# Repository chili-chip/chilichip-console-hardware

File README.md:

# chilichip console board

KiCad project for the all-in-one chilichip console PCB: the main board and all modules (RP2350, 2.0" screen, audio, radio, sensors, haptics, buttons) on one fully assembled board. 50 × 83.9 mm, 4 layers, fits the Slab casing.

**Status:** schematic, placement and routing done. 3 connections at the RP2350 still open (see docs, open points). Not built.

| Front | Back |
|---|---|
|  |  |

## Docs

The MkDocs site in `docs/` has the design, pin map, power tree, schematics, layout, parts list and open points. Run `pip install -r docs/requirements.txt && mkdocs serve`.

## Files

| Path | What it is |
|---|---|
| `chilichip-console.kicad_pro` and sheets | KiCad 10 project |
| `scripts/` | Generators: `design.py` holds every part and net |
| `reference/rp2350a-minimal/` | Raspberry Pi's RP2350A minimal design, unchanged |

## Credits

The RP2350A circuit comes from Raspberry Pi's **RP2350A minimal design** ([hardware design with RP2350](https://datasheets.raspberrypi.com/rp2350/hardware-design-with-rp2350.pdf)). Thanks to Raspberry Pi Ltd for publishing it. The GBA button footprints are from [Pigweed Kudzu](https://pigweed.googlesource.com/pigweed/kudzu/+/refs/heads/main/pcb/), CC BY 4.0.

## Licence

MIT, see [LICENSE.txt](LICENSE.txt). The copyright notice is Raspberry Pi Ltd's and stays in place; chilichip's changes are added next to it.

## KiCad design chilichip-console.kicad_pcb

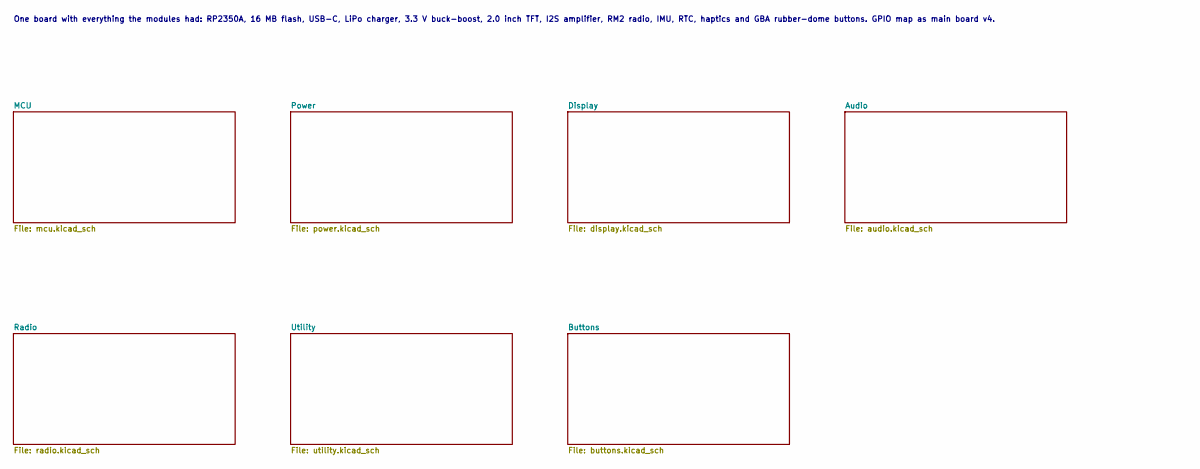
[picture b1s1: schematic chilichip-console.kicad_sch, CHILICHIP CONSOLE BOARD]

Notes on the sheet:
One board with everything the modules had: RP2350A, 16 MB flash, USB-C, LiPo charger, 3.3 V buck-boost, 2.0 inch TFT, I2S amplifier, RM2 radio, IMU, RTC, haptics and GBA rubber-dome buttons. GPIO map as main board v4.

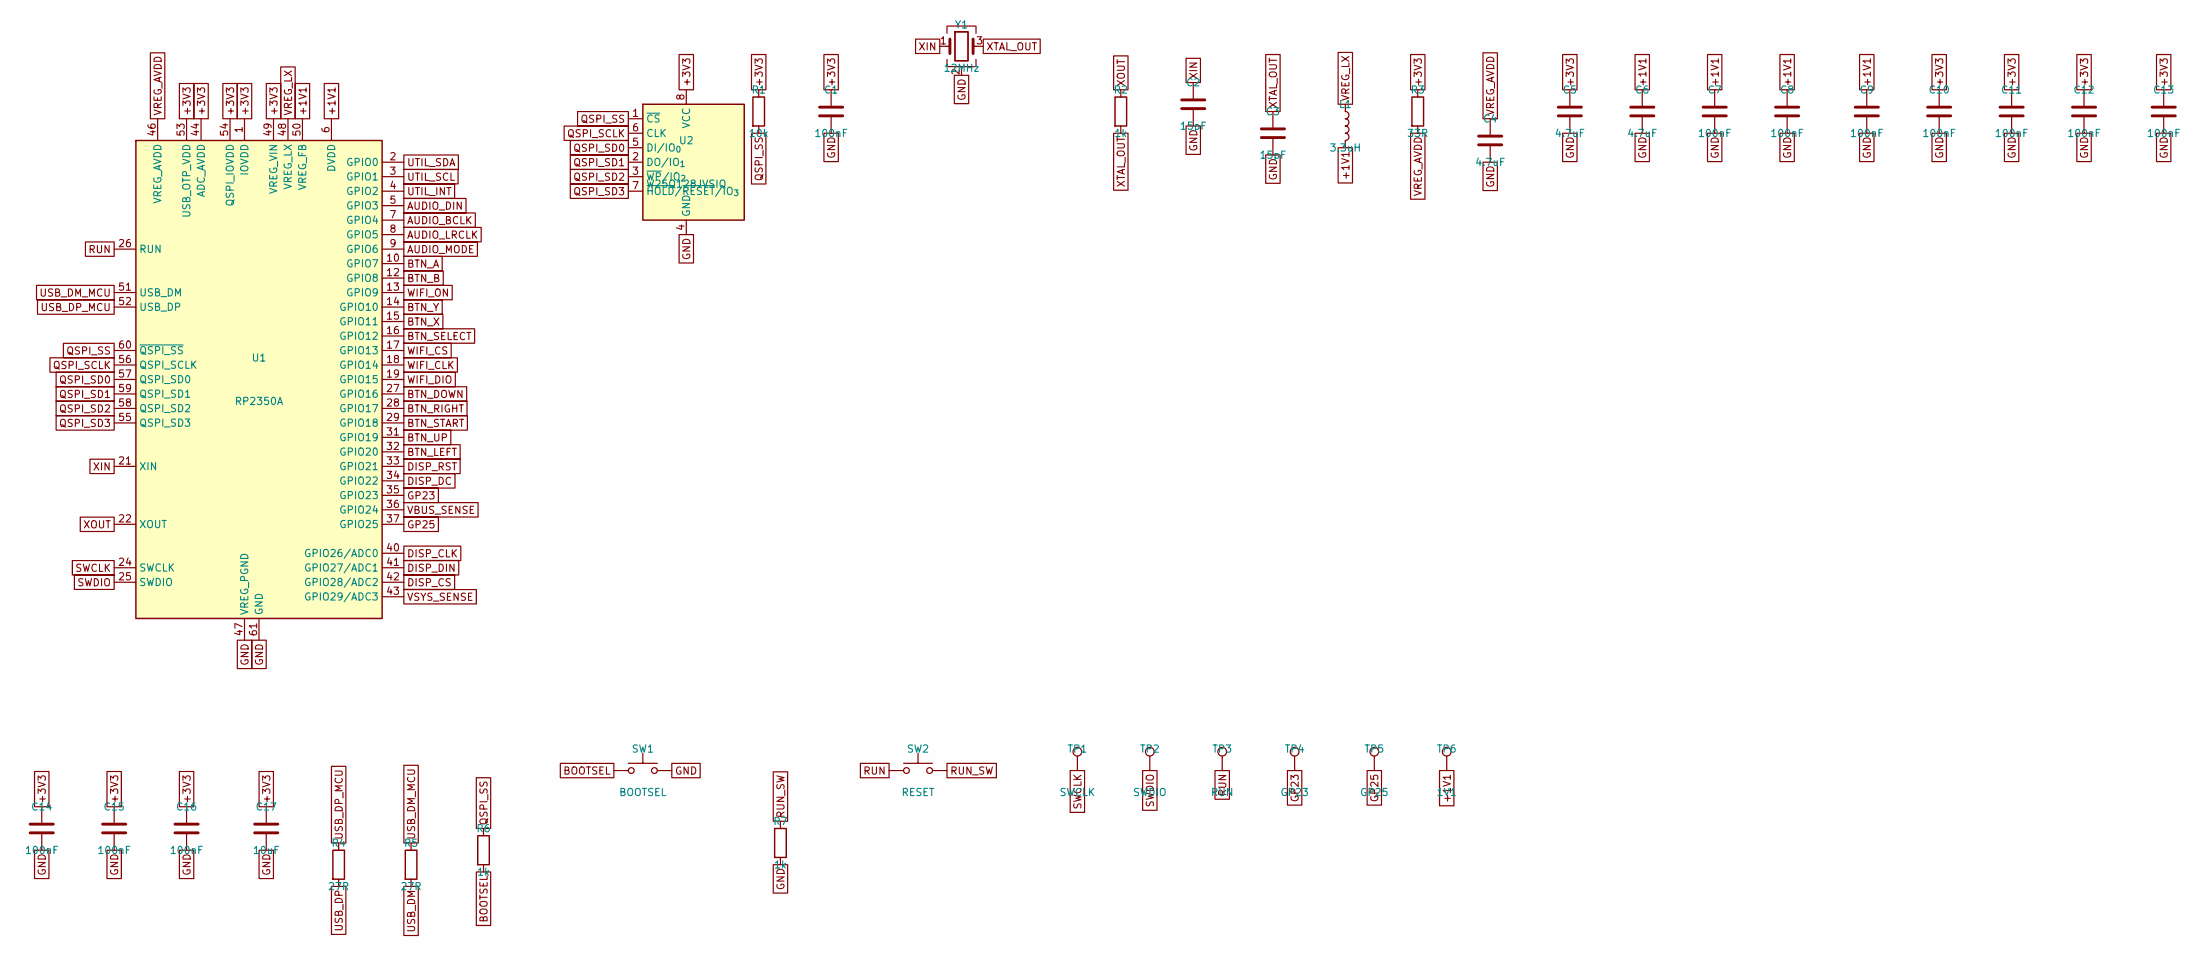
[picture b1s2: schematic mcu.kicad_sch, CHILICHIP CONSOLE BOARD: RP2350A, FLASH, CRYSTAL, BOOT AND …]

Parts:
C1, C7, C8, C9, C10, C11, C12, C13, C14, C15, C16: 100nF; C_0402_1005Metric; LCSC C1525
C2, C3: 15pF; C_0402_1005Metric; LCSC C1548
C4, C5, C6: 4.7uF; C_0402_1005Metric; LCSC C23733
C17: 10uF; C_0603_1608Metric; LCSC C19702
L1: 3.3uH; L_Abracon_AOTA-B201610S
R1: 10k; R_0402_1005Metric; LCSC C25744
R2, R6, R7: 1k; R_0402_1005Metric; LCSC C11702
R3: 33R; R_0402_1005Metric; LCSC C25105
R4, R5: 27R; R_0402_1005Metric; LCSC C25100
SW1: BOOTSEL; SW_Push_1P1T_XKB_TS-1187A; LCSC C318884
SW2: RESET; SW_Push_1P1T_XKB_TS-1187A; LCSC C318884
TP1: SWCLK; TestPoint_Pad_D1.0mm
TP2: SWDIO; TestPoint_Pad_D1.0mm
TP3: RUN; TestPoint_Pad_D1.0mm
TP4: GP23; TestPoint_Pad_D1.0mm
TP5: GP25; TestPoint_Pad_D1.0mm
TP6: 1V1; TestPoint_Pad_D1.0mm
U1: RP2350A; QFN-60-1EP_7x7mm_P0.4mm_EP3.4x3.4mm_ThermalVias; LCSC C42411118
U2: W25Q128JVSIQ; SOIC-8_5.3x5.3mm_P1.27mm; LCSC C97521
Y1: 12MHz; Crystal_SMD_3225-4Pin_3.2x2.5mm; LCSC C9002

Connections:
+1V1: C6.1, C7.1, C8.1, C9.1, L1.2, TP6.1, U1.6 (DVDD), U1.23 (DVDD), U1.39 (DVDD), U1.50 (VREG_FB)
+3V3: C1.1, C5.1, C10.1, C11.1, C12.1, C13.1, C14.1, C15.1, C16.1, C17.1, R1.1, R3.1, U1.1 (IOVDD), U1.11 (IOVDD), U1.20 (IOVDD), U1.30 (IOVDD), U1.38 (IOVDD), U1.44 (ADC_AVDD), U1.45 (IOVDD), U1.49 (VREG_VIN), U1.53 (USB_OTP_VDD), U1.54 (QSPI_IOVDD), U2.8 (VCC); also elsewhere on the board
AUDIO_BCLK: U1.7 (GPIO4); also elsewhere on the board
AUDIO_DIN: U1.5 (GPIO3); also elsewhere on the board
AUDIO_LRCLK: U1.8 (GPIO5); also elsewhere on the board
AUDIO_MODE: U1.9 (GPIO6); also elsewhere on the board
BOOTSEL: R6.2, SW1.1
BTN_A: U1.10 (GPIO7); also elsewhere on the board
BTN_B: U1.12 (GPIO8); also elsewhere on the board
BTN_DOWN: U1.27 (GPIO16); also elsewhere on the board
BTN_LEFT: U1.32 (GPIO20); also elsewhere on the board
BTN_RIGHT: U1.28 (GPIO17); also elsewhere on the board
BTN_SELECT: U1.16 (GPIO12); also elsewhere on the board
BTN_START: U1.29 (GPIO18); also elsewhere on the board
BTN_UP: U1.31 (GPIO19); also elsewhere on the board
BTN_X: U1.15 (GPIO11); also elsewhere on the board
BTN_Y: U1.14 (GPIO10); also elsewhere on the board
DISP_CLK: U1.40 (GPIO26/ADC0); also elsewhere on the board
DISP_CS: U1.42 (GPIO28/ADC2); also elsewhere on the board
DISP_DC: U1.34 (GPIO22); also elsewhere on the board
DISP_DIN: U1.41 (GPIO27/ADC1); also elsewhere on the board
DISP_RST: U1.33 (GPIO21); also elsewhere on the board
GND: C1.2, C2.2, C3.2, C4.2, C5.2, C6.2, C7.2, C8.2, C9.2, C10.2, C11.2, C12.2, C13.2, C14.2, C15.2, C16.2, C17.2, R7.2, SW1.2, U1.47 (VREG_PGND), U1.61 (GND), U2.4 (GND), Y1.2 (G), Y1.4 (G); also elsewhere on the board
GP23: TP4.1, U1.35 (GPIO23)
GP25: TP5.1, U1.37 (GPIO25)
QSPI_SCLK: U1.56 (QSPI_SCLK), U2.6 (CLK)
QSPI_SD0: U1.57 (QSPI_SD0), U2.5 (DI/IO_{0})
QSPI_SD1: U1.59 (QSPI_SD1), U2.2 (DO/IO_{1})
QSPI_SD2: U1.58 (QSPI_SD2), U2.3 (~WP/IO_{2})
QSPI_SD3: U1.55 (QSPI_SD3), U2.7 (~HOLD/~RESET/IO_{3})
QSPI_SS: R1.2, R6.1, U1.60 (~QSPI_SS), U2.1 (~CS)
RUN: SW2.1, TP3.1, U1.26 (RUN)
RUN_SW: R7.1, SW2.2
SWCLK: TP1.1, U1.24 (SWCLK)
SWDIO: TP2.1, U1.25 (SWDIO)
USB_DM: R5.2; also elsewhere on the board
USB_DM_MCU: R5.1, U1.51 (USB_DM)
USB_DP: R4.2; also elsewhere on the board
USB_DP_MCU: R4.1, U1.52 (USB_DP)
UTIL_INT: U1.4 (GPIO2); also elsewhere on the board
UTIL_SCL: U1.3 (GPIO1); also elsewhere on the board
UTIL_SDA: U1.2 (GPIO0); also elsewhere on the board
VBUS_SENSE: U1.36 (GPIO24); also elsewhere on the board
VREG_AVDD: C4.1, R3.2, U1.46 (VREG_AVDD)
VREG_LX: L1.1, U1.48 (VREG_LX)
VSYS_SENSE: U1.43 (GPIO29/ADC3); also elsewhere on the board
WIFI_CLK: U1.18 (GPIO14); also elsewhere on the board
WIFI_CS: U1.17 (GPIO13); also elsewhere on the board
WIFI_DIO: U1.19 (GPIO15); also elsewhere on the board
WIFI_ON: U1.13 (GPIO9); also elsewhere on the board
XIN: C2.1, U1.21 (XIN), Y1.1
XOUT: R2.1, U1.22 (XOUT)
XTAL_OUT: C3.1, R2.2, Y1.3

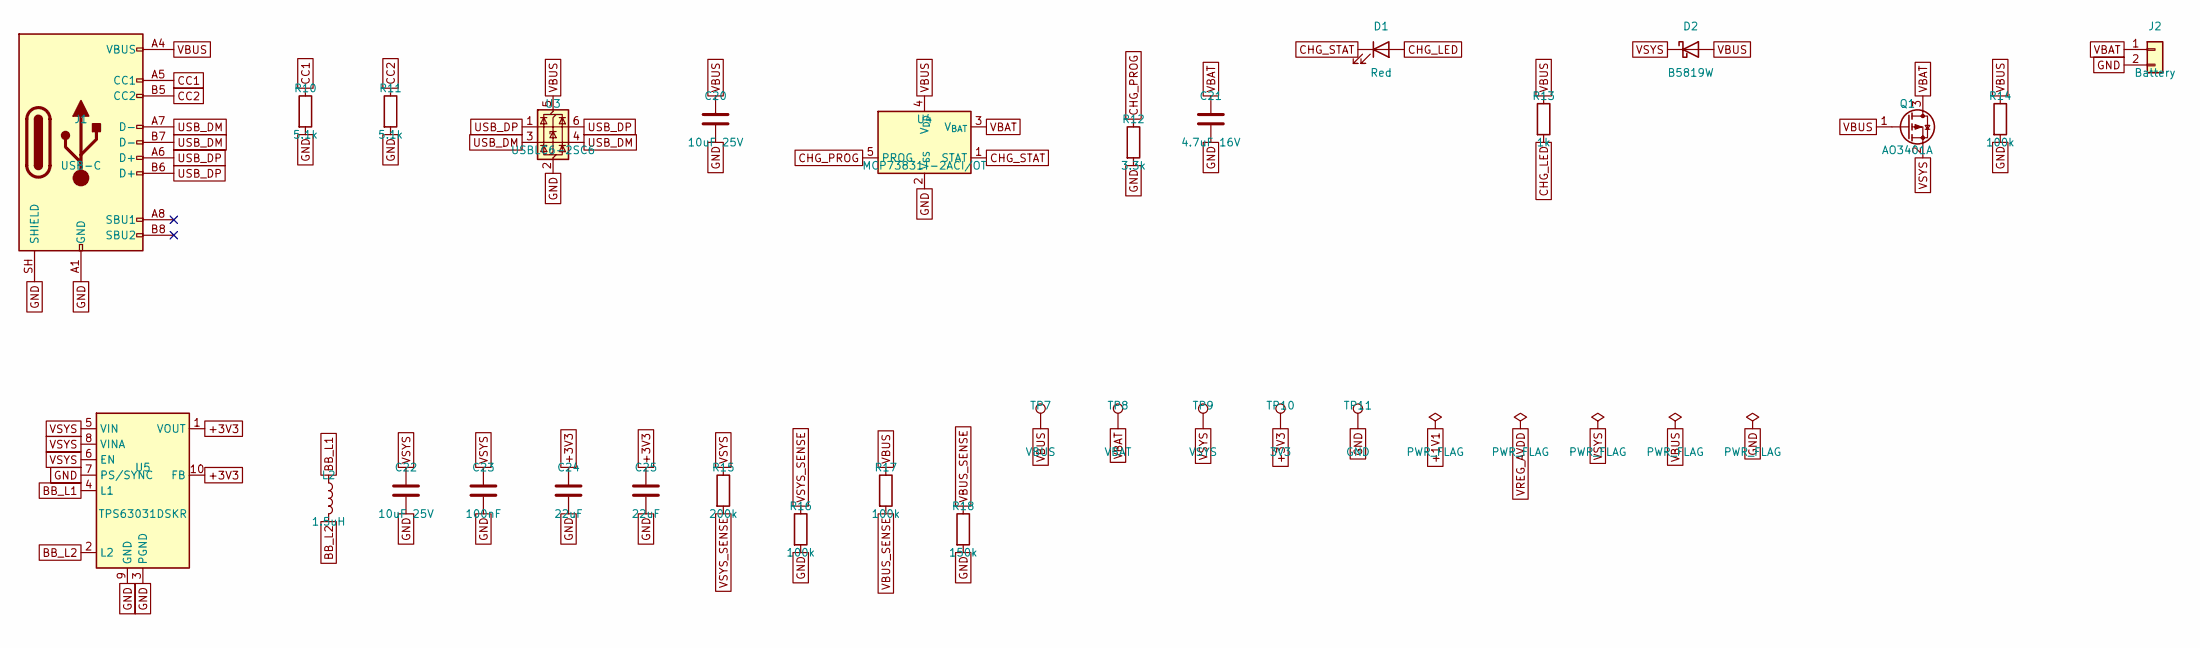
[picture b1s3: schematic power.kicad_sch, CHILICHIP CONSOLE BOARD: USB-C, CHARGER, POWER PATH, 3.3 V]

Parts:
C20, C22: 10uF 25V; C_0805_2012Metric; LCSC C15850
C21: 4.7uF 16V; C_0603_1608Metric; LCSC C19666
C23: 100nF; C_0402_1005Metric; LCSC C1525
C24, C25: 22uF; C_0805_2012Metric; LCSC C45783
D1: Red; LED_0603_1608Metric; LCSC C2286
D2: B5819W; D_SOD-123; LCSC C8598
J1: USB-C; USB_C_Receptacle_HRO_TYPE-C-31-M-12; LCSC C165948
J2: Battery; Molex_PicoBlade_53261-0271_1x02-1MP_P1.25mm_Horizontal; LCSC C177225
L2: 1.5uH; L_APV_ANR252012
Q1: AO3401A; SOT-23; LCSC C15127
R10, R11: 5.1k; R_0402_1005Metric; LCSC C25905
R12: 3.3k; R_0402_1005Metric; LCSC C25890
R13: 1k; R_0402_1005Metric; LCSC C11702
R14, R16, R17: 100k; R_0402_1005Metric; LCSC C25741
R15: 200k; R_0402_1005Metric; LCSC C25764
R18: 150k; R_0402_1005Metric; LCSC C25755
TP7: VBUS; TestPoint_Pad_D1.0mm
TP8: VBAT; TestPoint_Pad_D1.0mm
TP9: VSYS; TestPoint_Pad_D1.0mm
TP10: 3V3; TestPoint_Pad_D1.0mm
TP11: GND; TestPoint_Pad_D1.0mm
U3: USBLC6-2SC6; SOT-23-6; LCSC C7519
U4: MCP73831T-2ACI/OT; SOT-23-5; LCSC C424093
U5: TPS63031DSKR; WSON-10-1EP_2.5x2.5mm_P0.5mm_EP1.2x2mm_ThermalVias

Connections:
+3V3: C24.1, C25.1, TP10.1, U5.1 (VOUT), U5.10 (FB); also elsewhere on the board
BB_L1: L2.1, U5.4 (L1)
BB_L2: L2.2, U5.2 (L2)
CC1: J1.A5 (CC1), R10.1
CC2: J1.B5 (CC2), R11.1
CHG_LED: D1.2 (A), R13.2
CHG_PROG: R12.1, U4.5 (PROG)
CHG_STAT: D1.1 (K), U4.1 (STAT)
GND: C20.2, C21.2, C22.2, C23.2, C24.2, C25.2, J1.A1 (GND), J1.A12 (GND), J1.B1 (GND), J1.B12 (GND), J1.SH (SHIELD), J2.2, R10.2, R11.2, R12.2, R14.2, R16.2, R18.2, TP11.1, U3.2 (GND), U4.2 (V_{SS}), U5.3 (PGND), U5.7 (PS/SYNC), U5.9 (GND), U5.11 (PGND); also elsewhere on the board
USB_DM: J1.A7 (D-), J1.B7 (D-), U3.3 (I/O2), U3.4 (I/O2); also elsewhere on the board
USB_DP: J1.A6 (D+), J1.B6 (D+), U3.1 (I/O1), U3.6 (I/O1); also elsewhere on the board
VBAT: C21.1, J2.1, Q1.3 (D), TP8.1, U4.3 (V_{BAT})
VBUS: C20.1, D2.2 (A), J1.A4 (VBUS), J1.A9 (VBUS), J1.B4 (VBUS), J1.B9 (VBUS), Q1.1 (G), R13.1, R14.1, R17.1, TP7.1, U3.5 (VBUS), U4.4 (V_{DD})
VBUS_SENSE: R17.2, R18.1; also elsewhere on the board
VSYS: C22.1, C23.1, D2.1 (K), Q1.2 (S), R15.1, TP9.1, U5.5 (VIN), U5.6 (EN), U5.8 (VINA); also elsewhere on the board
VSYS_SENSE: R15.2, R16.1; also elsewhere on the board

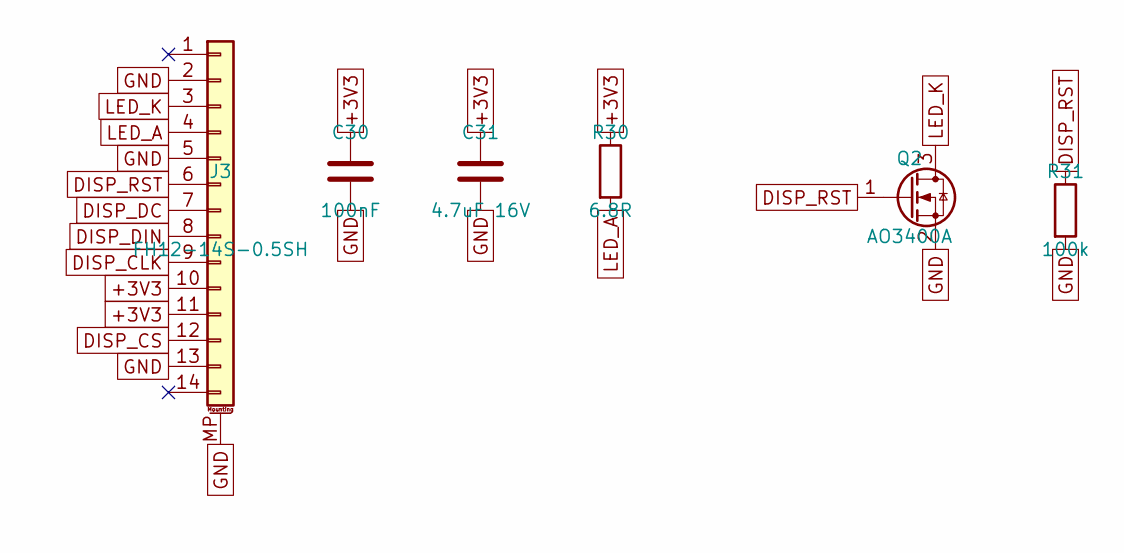
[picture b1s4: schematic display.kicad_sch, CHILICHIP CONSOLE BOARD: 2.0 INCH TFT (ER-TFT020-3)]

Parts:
C30: 100nF; C_0402_1005Metric; LCSC C1525
C31: 4.7uF 16V; C_0603_1608Metric; LCSC C19666
J3: FH12-14S-0.5SH; Hirose_FH12-14S-0.5SH_1x14-1MP_P0.50mm_Horizontal
Q2: AO3400A; SOT-23; LCSC C20917
R30: 6.8R; R_0603_1608Metric
R31: 100k; R_0402_1005Metric; LCSC C25741

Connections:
+3V3: C30.1, C31.1, J3.10, J3.11, R30.1; also elsewhere on the board
DISP_CLK: J3.9; also elsewhere on the board
DISP_CS: J3.12; also elsewhere on the board
DISP_DC: J3.7; also elsewhere on the board
DISP_DIN: J3.8; also elsewhere on the board
DISP_RST: J3.6, Q2.1 (G), R31.1; also elsewhere on the board
GND: C30.2, C31.2, J3.2, J3.5, J3.13, J3.MP (MountPin), Q2.2 (S), R31.2; also elsewhere on the board
LED_A: J3.4, R30.2
LED_K: J3.3, Q2.3 (D)

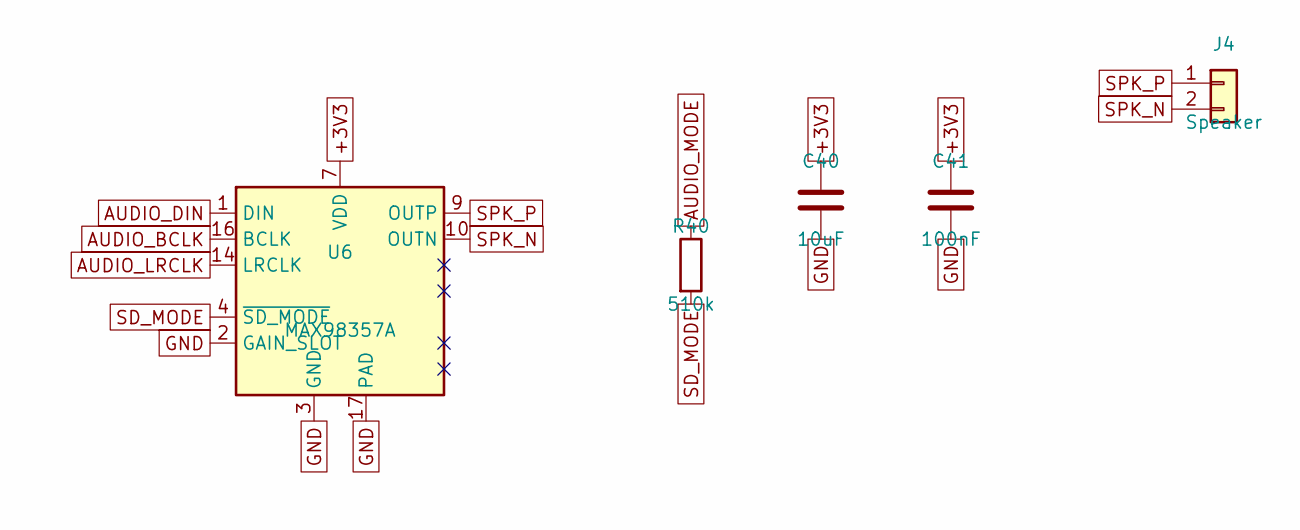
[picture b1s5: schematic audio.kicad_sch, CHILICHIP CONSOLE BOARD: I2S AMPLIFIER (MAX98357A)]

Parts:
C40: 10uF; C_0603_1608Metric; LCSC C19702
C41: 100nF; C_0402_1005Metric; LCSC C1525
J4: Speaker; Molex_PicoBlade_53261-0271_1x02-1MP_P1.25mm_Horizontal; LCSC C177225
R40: 510k; R_0603_1608Metric; LCSC C23192
U6: MAX98357A; TQFN-16-1EP_3x3mm_P0.5mm_EP1.23x1.23mm_ThermalVias; LCSC C910544

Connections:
+3V3: C40.1, C41.1, U6.7 (VDD), U6.8 (VDD); also elsewhere on the board
AUDIO_BCLK: U6.16 (BCLK); also elsewhere on the board
AUDIO_DIN: U6.1 (DIN); also elsewhere on the board
AUDIO_LRCLK: U6.14 (LRCLK); also elsewhere on the board
AUDIO_MODE: R40.1; also elsewhere on the board
GND: C40.2, C41.2, U6.2 (GAIN_SLOT), U6.3 (GND), U6.11 (GND), U6.15 (GND), U6.17 (PAD); also elsewhere on the board
SD_MODE: R40.2, U6.4 (~SD_MODE)
SPK_N: J4.2, U6.10 (OUTN)
SPK_P: J4.1, U6.9 (OUTP)

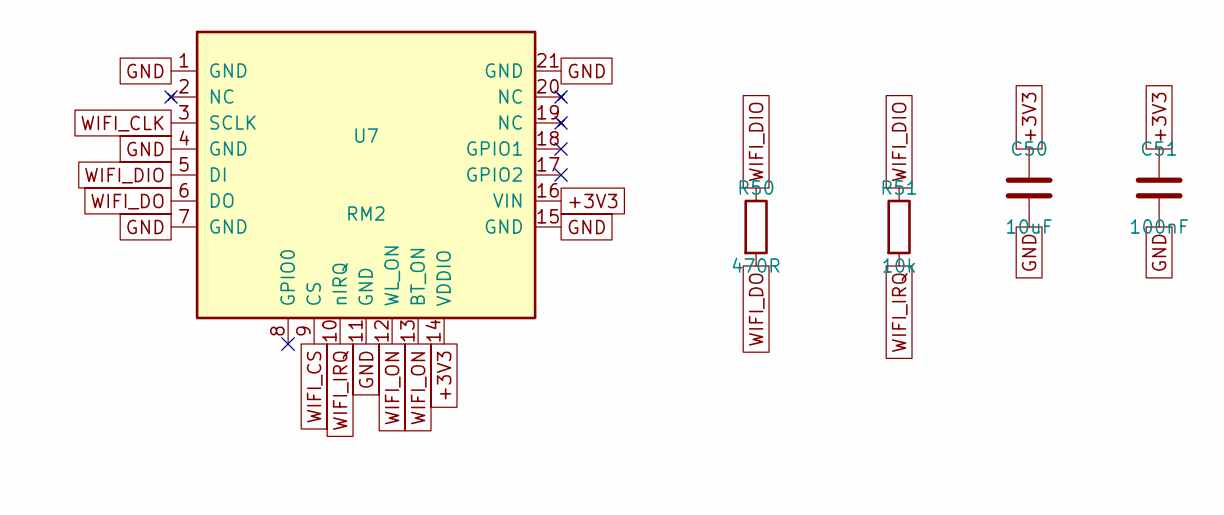
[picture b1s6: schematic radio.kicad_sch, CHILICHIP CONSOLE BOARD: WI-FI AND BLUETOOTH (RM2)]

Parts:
C50: 10uF; C_0603_1608Metric; LCSC C19702
C51: 100nF; C_0402_1005Metric; LCSC C1525
R50: 470R; R_0402_1005Metric; LCSC C25117
R51: 10k; R_0402_1005Metric; LCSC C25744
U7: RM2; RMC20452T

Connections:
+3V3: C50.1, C51.1, U7.14 (VDDIO), U7.16 (VIN); also elsewhere on the board
GND: C50.2, C51.2, U7.1 (GND), U7.4 (GND), U7.7 (GND), U7.11 (GND), U7.15 (GND), U7.21 (GND); also elsewhere on the board
WIFI_CLK: U7.3 (SCLK); also elsewhere on the board
WIFI_CS: U7.9 (CS); also elsewhere on the board
WIFI_DIO: R50.1, R51.1, U7.5 (DI); also elsewhere on the board
WIFI_DO: R50.2, U7.6 (DO)
WIFI_IRQ: R51.2, U7.10 (nIRQ)
WIFI_ON: U7.12 (WL_ON), U7.13 (BT_ON); also elsewhere on the board

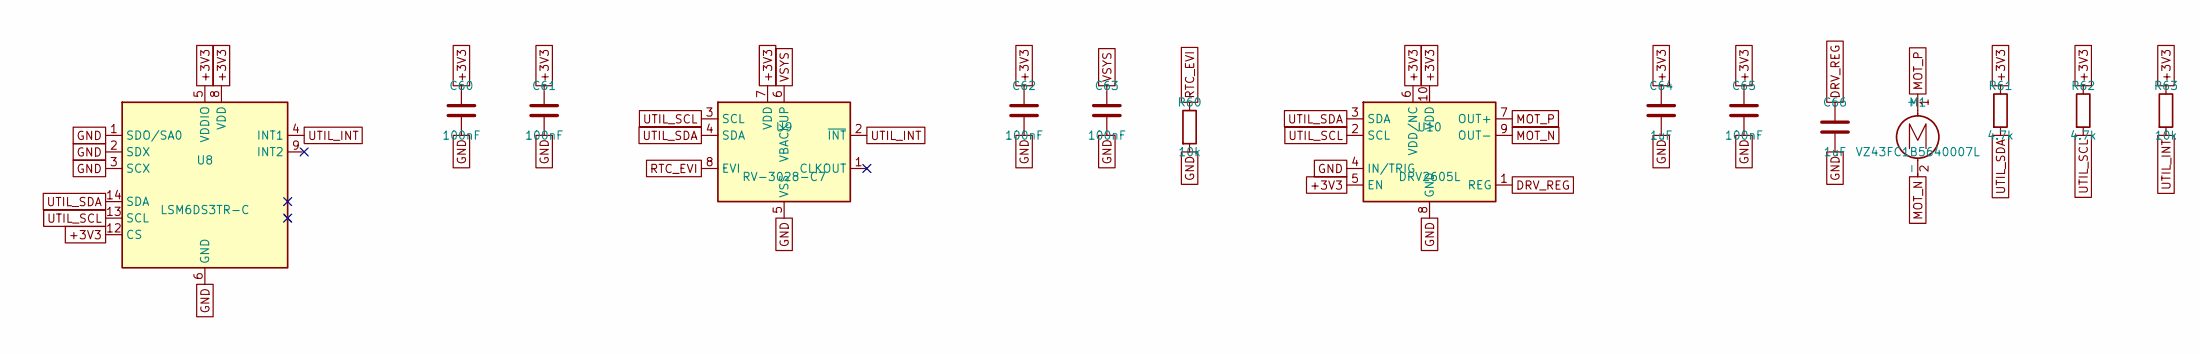
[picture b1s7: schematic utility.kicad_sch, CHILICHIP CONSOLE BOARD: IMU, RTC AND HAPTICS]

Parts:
C60, C61, C62, C63, C65: 100nF; C_0402_1005Metric; LCSC C1525
C64, C66: 1uF; C_0402_1005Metric; LCSC C52923
M1: VZ43FC1B5640007L; Motor_ERM_SMD_Vybronics_VZ43FC1B
R60, R63: 10k; R_0402_1005Metric; LCSC C25744
R61, R62: 4.7k; R_0402_1005Metric; LCSC C25900
U8: LSM6DS3TR-C; LGA-14_3x2.5mm_P0.5mm_LayoutBorder3x4y; LCSC C967633
U9: RV-3028-C7; MicroCrystal_C7_SON-8_1.5x3.2mm_P0.9mm; LCSC C3019759
U10: DRV2605L; TSSOP-10_3x3mm_P0.5mm; LCSC C527464

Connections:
+3V3: C60.1, C61.1, C62.1, C64.1, C65.1, R61.1, R62.1, R63.1, U8.5 (VDDIO), U8.8 (VDD), U8.12 (CS), U9.7 (VDD), U10.5 (EN), U10.6 (VDD/NC), U10.10 (VDD); also elsewhere on the board
DRV_REG: C66.1, U10.1 (REG)
GND: C60.2, C61.2, C62.2, C63.2, C64.2, C65.2, C66.2, R60.2, U8.1 (SDO/SA0), U8.2 (SDX), U8.3 (SCX), U8.6 (GND), U8.7 (GND), U9.5 (VSS), U10.4 (IN/TRIG), U10.8 (GND); also elsewhere on the board
MOT_N: M1.2 (-), U10.9 (OUT-)
MOT_P: M1.1 (+), U10.7 (OUT+)
RTC_EVI: R60.1, U9.8 (EVI)
UTIL_INT: R63.2, U8.4 (INT1), U9.2 (~INT); also elsewhere on the board
UTIL_SCL: R62.2, U8.13 (SCL), U9.3 (SCL), U10.2 (SCL); also elsewhere on the board
UTIL_SDA: R61.2, U8.14 (SDA), U9.4 (SDA), U10.3 (SDA); also elsewhere on the board
VSYS: C63.1, U9.6 (VBACKUP); also elsewhere on the board

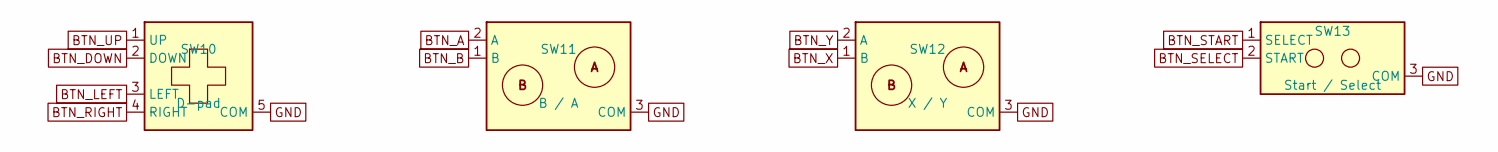
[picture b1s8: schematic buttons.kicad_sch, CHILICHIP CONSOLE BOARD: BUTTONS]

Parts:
SW10: D-pad; GBA_DPad
SW11: B / A; GBA_AB
SW12: X / Y; GBA_AB
SW13: Start / Select; GBA_StartSelect

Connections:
BTN_A: SW11.2 (A); also elsewhere on the board
BTN_B: SW11.1 (B); also elsewhere on the board
BTN_DOWN: SW10.2 (DOWN); also elsewhere on the board
BTN_LEFT: SW10.3 (LEFT); also elsewhere on the board
BTN_RIGHT: SW10.4 (RIGHT); also elsewhere on the board
BTN_SELECT: SW13.2 (START); also elsewhere on the board
BTN_START: SW13.1 (SELECT); also elsewhere on the board
BTN_UP: SW10.1 (UP); also elsewhere on the board
BTN_X: SW12.1 (B); also elsewhere on the board
BTN_Y: SW12.2 (A); also elsewhere on the board
GND: SW10.5 (COM), SW11.3 (COM), SW12.3 (COM), SW13.3 (COM); also elsewhere on the board

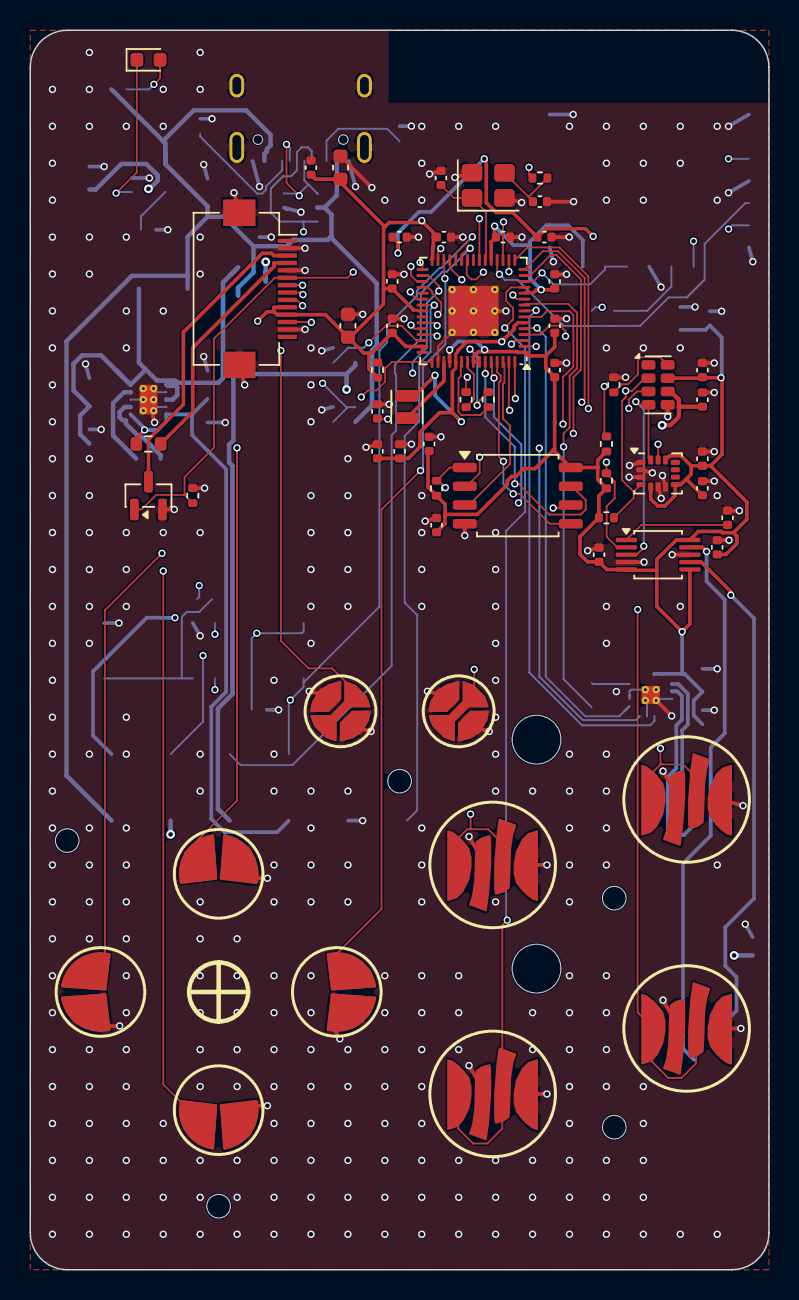
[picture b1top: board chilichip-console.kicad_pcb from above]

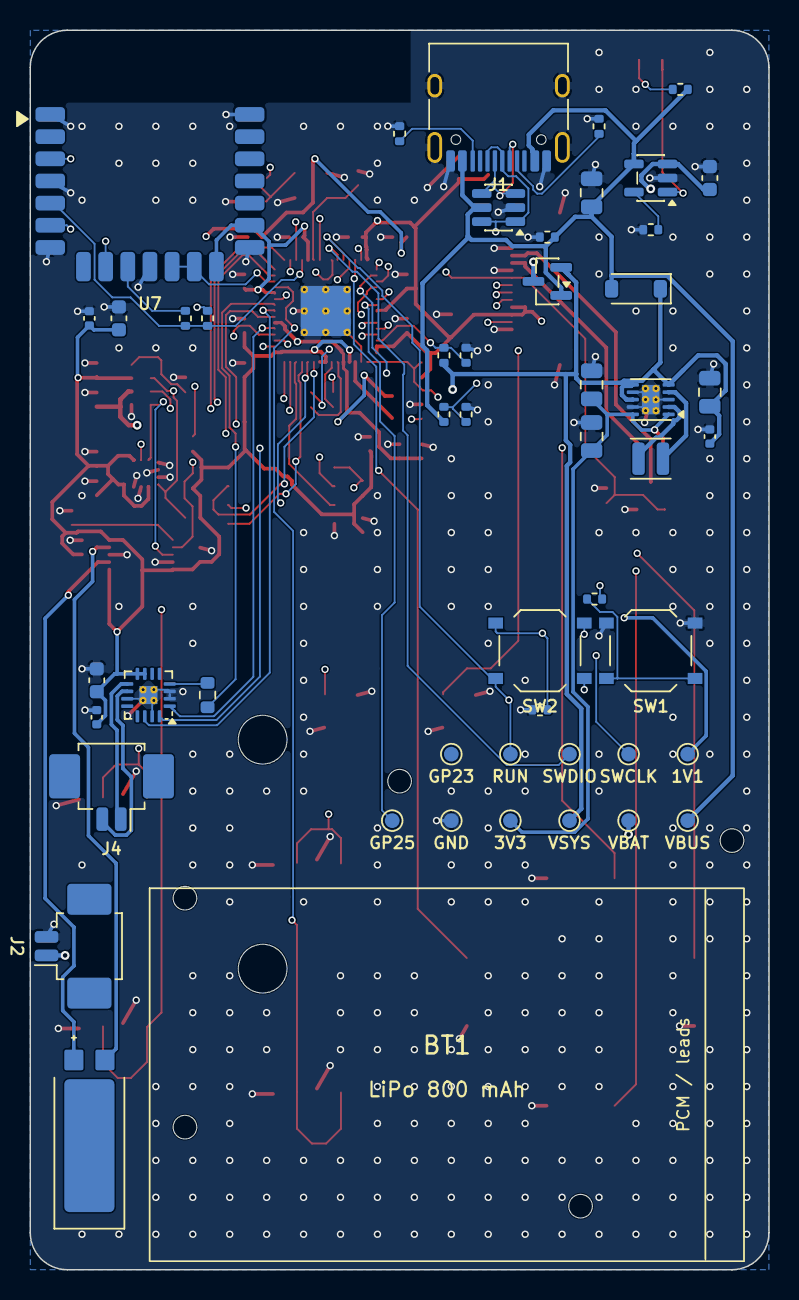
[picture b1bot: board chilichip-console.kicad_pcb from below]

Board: 4 copper layers, 50.0 x 83.9 mm, 101 parts (50 on the bottom side), 74 nets.

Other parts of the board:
BT1: 502540; LiPo_502540

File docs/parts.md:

# Parts list

Generated from `scripts/design.py` with `python3 scripts/bom.py`. LCSC numbers were checked on lcsc.com on 27 Nov 2026. "To source" means the part is not stocked there or the number is not picked yet.

The button contacts (SW10 to SW13), test pads and the battery outline are copper or drawings only, so they are not in the list.

| Block | Refs | Qty | Value | Footprint | LCSC |
|---|---|---|---|---|---|
| MCU | U1 | 1 | RP2350A | `QFN-60-1EP_7x7mm_P0.4mm_EP3.4x3.4mm_ThermalVias` | [C42411118](https://www.lcsc.com/product-detail/C42411118.html) |
| MCU | U2 | 1 | W25Q128JVSIQ | `SOIC-8_5.3x5.3mm_P1.27mm` | [C97521](https://www.lcsc.com/product-detail/C97521.html) |
| MCU | R1 | 1 | 10k | `R_0402_1005Metric` | [C25744](https://www.lcsc.com/product-detail/C25744.html) |
| MCU | C1, C7, C8, C9, C10, C11, C12, C13, C14, C15, C16 | 11 | 100nF | `C_0402_1005Metric` | [C1525](https://www.lcsc.com/product-detail/C1525.html) |
| MCU | Y1 | 1 | 12MHz | `Crystal_SMD_3225-4Pin_3.2x2.5mm` | [C9002](https://www.lcsc.com/product-detail/C9002.html) |
| MCU | R2, R6, R7 | 3 | 1k | `R_0402_1005Metric` | [C11702](https://www.lcsc.com/product-detail/C11702.html) |
| MCU | C2, C3 | 2 | 15pF | `C_0402_1005Metric` | [C1548](https://www.lcsc.com/product-detail/C1548.html) |
| MCU | L1 | 1 | 3.3uH | `L_Abracon_AOTA-B201610S` | to source |
| MCU | R3 | 1 | 33R | `R_0402_1005Metric` | [C25105](https://www.lcsc.com/product-detail/C25105.html) |
| MCU | C4, C5, C6 | 3 | 4.7uF | `C_0402_1005Metric` | [C23733](https://www.lcsc.com/product-detail/C23733.html) |
| MCU | C17 | 1 | 10uF | `C_0603_1608Metric` | [C19702](https://www.lcsc.com/product-detail/C19702.html) |
| MCU | R4, R5 | 2 | 27R | `R_0402_1005Metric` | [C25100](https://www.lcsc.com/product-detail/C25100.html) |
| MCU | SW1 | 1 | BOOTSEL | `SW_Push_1P1T_XKB_TS-1187A` | [C318884](https://www.lcsc.com/product-detail/C318884.html) |
| MCU | SW2 | 1 | RESET | `SW_Push_1P1T_XKB_TS-1187A` | [C318884](https://www.lcsc.com/product-detail/C318884.html) |
| Power | J1 | 1 | USB-C | `USB_C_Receptacle_HRO_TYPE-C-31-M-12` | [C165948](https://www.lcsc.com/product-detail/C165948.html) |
| Power | R10, R11 | 2 | 5.1k | `R_0402_1005Metric` | [C25905](https://www.lcsc.com/product-detail/C25905.html) |
| Power | U3 | 1 | USBLC6-2SC6 | `SOT-23-6` | [C7519](https://www.lcsc.com/product-detail/C7519.html) |
| Power | C20, C22 | 2 | 10uF 25V | `C_0805_2012Metric` | [C15850](https://www.lcsc.com/product-detail/C15850.html) |
| Power | U4 | 1 | MCP73831T-2ACI/OT | `SOT-23-5` | [C424093](https://www.lcsc.com/product-detail/C424093.html) |
| Power | R12 | 1 | 3.3k | `R_0402_1005Metric` | [C25890](https://www.lcsc.com/product-detail/C25890.html) |
| Power | C21 | 1 | 4.7uF 16V | `C_0603_1608Metric` | [C19666](https://www.lcsc.com/product-detail/C19666.html) |
| Power | D1 | 1 | Red | `LED_0603_1608Metric` | [C2286](https://www.lcsc.com/product-detail/C2286.html) |
| Power | R13 | 1 | 1k | `R_0402_1005Metric` | [C11702](https://www.lcsc.com/product-detail/C11702.html) |
| Power | D2 | 1 | B5819W | `D_SOD-123` | [C8598](https://www.lcsc.com/product-detail/C8598.html) |
| Power | Q1 | 1 | AO3401A | `SOT-23` | [C15127](https://www.lcsc.com/product-detail/C15127.html) |
| Power | R14, R16, R17 | 3 | 100k | `R_0402_1005Metric` | [C25741](https://www.lcsc.com/product-detail/C25741.html) |
| Power | J2 | 1 | Battery | `Molex_PicoBlade_53261-0271_1x02-1MP_P1.25mm_Horizontal` | [C177225](https://www.lcsc.com/product-detail/C177225.html) |
| Power | U5 | 1 | TPS63031DSKR | `WSON-10-1EP_2.5x2.5mm_P0.5mm_EP1.2x2mm_ThermalVias` | to source |
| Power | L2 | 1 | 1.5uH | `L_APV_ANR252012` | to source |
| Power | C23 | 1 | 100nF | `C_0402_1005Metric` | [C1525](https://www.lcsc.com/product-detail/C1525.html) |
| Power | C24, C25 | 2 | 22uF | `C_0805_2012Metric` | [C45783](https://www.lcsc.com/product-detail/C45783.html) |
| Power | R15 | 1 | 200k | `R_0402_1005Metric` | [C25764](https://www.lcsc.com/product-detail/C25764.html) |
| Power | R18 | 1 | 150k | `R_0402_1005Metric` | [C25755](https://www.lcsc.com/product-detail/C25755.html) |
| Display | J3 | 1 | FH12-14S-0.5SH | `Hirose_FH12-14S-0.5SH_1x14-1MP_P0.50mm_Horizontal` | to source |
| Display | C30 | 1 | 100nF | `C_0402_1005Metric` | [C1525](https://www.lcsc.com/product-detail/C1525.html) |
| Display | C31 | 1 | 4.7uF 16V | `C_0603_1608Metric` | [C19666](https://www.lcsc.com/product-detail/C19666.html) |
| Display | R30 | 1 | 6.8R | `R_0603_1608Metric` | to source |
| Display | Q2 | 1 | AO3400A | `SOT-23` | [C20917](https://www.lcsc.com/product-detail/C20917.html) |
| Display | R31 | 1 | 100k | `R_0402_1005Metric` | [C25741](https://www.lcsc.com/product-detail/C25741.html) |
| Audio | U6 | 1 | MAX98357A | `TQFN-16-1EP_3x3mm_P0.5mm_EP1.23x1.23mm_ThermalVias` | [C910544](https://www.lcsc.com/product-detail/C910544.html) |
| Audio | R40 | 1 | 510k | `R_0603_1608Metric` | [C23192](https://www.lcsc.com/product-detail/C23192.html) |
| Audio | C40 | 1 | 10uF | `C_0603_1608Metric` | [C19702](https://www.lcsc.com/product-detail/C19702.html) |
| Audio | C41 | 1 | 100nF | `C_0402_1005Metric` | [C1525](https://www.lcsc.com/product-detail/C1525.html) |
| Audio | J4 | 1 | Speaker | `Molex_PicoBlade_53261-0271_1x02-1MP_P1.25mm_Horizontal` | [C177225](https://www.lcsc.com/product-detail/C177225.html) |
| Radio | U7 | 1 | RM2 | `RMC20452T` | to source |
| Radio | R50 | 1 | 470R | `R_0402_1005Metric` | [C25117](https://www.lcsc.com/product-detail/C25117.html) |
| Radio | R51 | 1 | 10k | `R_0402_1005Metric` | [C25744](https://www.lcsc.com/product-detail/C25744.html) |
| Radio | C50 | 1 | 10uF | `C_0603_1608Metric` | [C19702](https://www.lcsc.com/product-detail/C19702.html) |
| Radio | C51 | 1 | 100nF | `C_0402_1005Metric` | [C1525](https://www.lcsc.com/product-detail/C1525.html) |
| Utility | U8 | 1 | LSM6DS3TR-C | `LGA-14_3x2.5mm_P0.5mm_LayoutBorder3x4y` | [C967633](https://www.lcsc.com/product-detail/C967633.html) |
| Utility | C60, C61, C62, C63, C65 | 5 | 100nF | `C_0402_1005Metric` | [C1525](https://www.lcsc.com/product-detail/C1525.html) |
| Utility | U9 | 1 | RV-3028-C7 | `MicroCrystal_C7_SON-8_1.5x3.2mm_P0.9mm` | [C3019759](https://www.lcsc.com/product-detail/C3019759.html) |
| Utility | R60, R63 | 2 | 10k | `R_0402_1005Metric` | [C25744](https://www.lcsc.com/product-detail/C25744.html) |
| Utility | U10 | 1 | DRV2605L | `TSSOP-10_3x3mm_P0.5mm` | [C527464](https://www.lcsc.com/product-detail/C527464.html) |
| Utility | C64, C66 | 2 | 1uF | `C_0402_1005Metric` | [C52923](https://www.lcsc.com/product-detail/C52923.html) |
| Utility | M1 | 1 | VZ43FC1B5640007L | `Motor_ERM_SMD_Vybronics_VZ43FC1B` | to source |
| Utility | R61, R62 | 2 | 4.7k | `R_0402_1005Metric` | [C25900](https://www.lcsc.com/product-detail/C25900.html) |

## Not on the board

| Part | Where it goes | Source |
|---|---|---|
| ER-TFT020-3 2.0" TFT | Casing frame, FPC into J3 | [buydisplay](https://www.buydisplay.com/) |
| 502540 LiPo with protection board and PicoBlade plug | Back, into J2 | Several sellers; check the plug polarity |
| Speaker (as today) | Casing, into J4 | |
| GBA silicone pads and caps | Front, over SW10 to SW13 | GBA replacement parts |

## To source

| Ref | Part | Note |
|---|---|---|
| U5 | TI TPS63031DSKR | Pick an LCSC number before ordering |
| L1 | Abracon AOTA-B201610S3R3-101-T | The part Raspberry Pi specifies for the RP2350 switcher. Keep it |
| L2 | 1.5 µH, 2.5 × 2.0 mm, Isat ≥ 1.5 A | Any power inductor with this footprint |
| J3 | Hirose FH12-14S-0.5SH(55) | Same as the display module |
| R30 | 6.8 Ω 0603 | Same as the display module |
| U7 | Raspberry Pi RM2 | Raspberry Pi resellers, or consign to JLCPCB |
| M1 | Vybronics VZ43FC1B5640007L | Digi-Key 12323649, consign to JLCPCB |
| U2 | W25Q128JVSIQ | C97521 shows no stock today; check again or use the USON version |
